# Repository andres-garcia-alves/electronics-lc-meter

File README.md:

# LC Meter v2.0

A Capacimeter + Inductometer based on Arduino Nano.  
Capacitor measurement with 3 working modes: accuracy (slow), balanced and speed.  

Case 3D model included ;-)

This proyect was inspired on video [Medidor de Bobinas/Inductores y Capacitores con Arduino y Display LCD](https://www.youtube.com/watch?v=hMa-AWyuxaA) (spanish) from [Electgpl](https://www.youtube.com/@electgpl) YouTube channel.

&nbsp;

This project use the following electronic components:
- 1 x Arduino Nano v3.0
- 1 x LCD Display 16x2
- 1 x LCD Display I2C Module
- 1 x LM358 Operational Amplifier
- 1 x Capacitor 1uF
- 1 x Switch Button (2 positions)
- 3 x Push Button
- 1 x 220 ohm resistor
- 1 x 470 ohm resistor
- 1 x 10K ohm resistor
- 1 x 100K ohm resistor
- 1 x 1M ohm resistor
- 14 x pin-header 90 degress
- 2 x Bornier x2 (optional)
- 1 x DC conector (optional power 5-12V)
- 2 x Alligator clip conector (optional external measurement)
- wires

&nbsp;

### Screenshots

| Diagram - Schematics                            | Diagram - PCB                                   |
|-------------------------------------------------|-------------------------------------------------|
|          |                |

| Diagram - PCB Render                            | Diagram - PCB Render                            |
|-------------------------------------------------|-------------------------------------------------|
|      |       |

| Prototype                                       | Prototype                                       |
|-------------------------------------------------|-------------------------------------------------|
|                  |                  |

| PCB Manufacturing                               | Project Assembly                                |
|-------------------------------------------------|-------------------------------------------------|
|          |               |

| PCB Assembly                                    | PCB Assembly                                    |
|-------------------------------------------------|-------------------------------------------------|
|               |               |

| Case 3D model                                   | Project Final                                   |
|-------------------------------------------------|-------------------------------------------------|
|              |              |

| Capacimeter (YouTube video)                     | Inductometer (YouTube video)                    |
|-------------------------------------------------|-------------------------------------------------|
|  |  |

See 'Rescources' sub-folder for more pictures & videos of the project.

&nbsp;

### Version History

v1.0 (2024.03.02) - Initial release.  
v1.1 (2024.03.03) - Adding case 3D model.  
v1.2 (2024.03.09) - Pin position & component annotations improvements.  
v1.3 (2025.12.20) - Update project structure.  
v1.4 (2025.12.26) - Adding 'Stickers' folder.  

&nbsp;

This source code is licensed under GPL v3.0  
Please send me your feedback about this project: andres.garcia.alves@gmail.com

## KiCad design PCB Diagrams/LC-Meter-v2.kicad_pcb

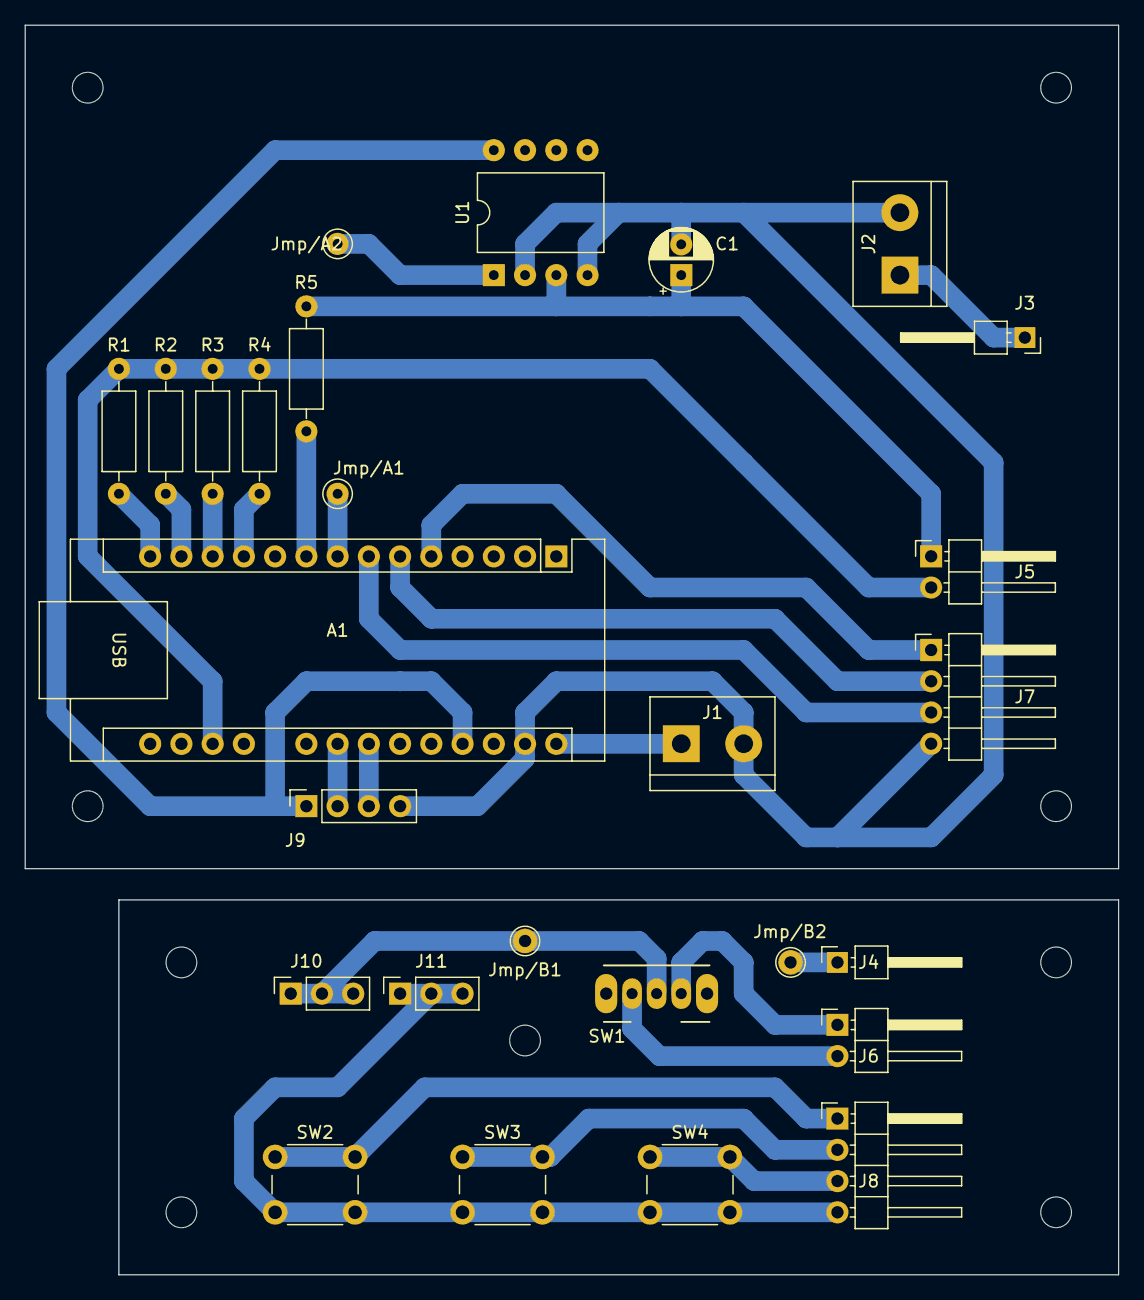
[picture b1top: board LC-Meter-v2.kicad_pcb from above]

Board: 2 copper layers, 88.9 x 101.6 mm, 36 parts (0 on the bottom side), 26 nets.

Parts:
A1: Arduino Nano v3; Arduino_Nano
C1: 1uF; CP_Radial_D5.0mm_P2.50mm
H1, H2, H3, H4: Base Hole; MountingHole_2.5mm
H5, H6, H7, H8, H9: Top Hole; MountingHole_2.5mm
J1: Power; TerminalBlock_bornier-2_P5.08mm
J2: External; TerminalBlock_bornier-2_P5.08mm
J3: Ext/A; PinHeader_1x01_P2.54mm_Horizontal
J4: Ext/B; PinHeader_1x01_P2.54mm_Horizontal
J5: Select/A; PinHeader_1x02_P2.54mm_Horizontal
J6: Select/B; PinHeader_1x02_P2.54mm_Horizontal
J7: CxMode/A; PinHeader_1x04_P2.54mm_Horizontal
J8: CxMode/B; PinHeader_1x04_P2.54mm_Horizontal
J9: Display I2C; PinSocket_1x04_P2.54mm_Vertical
J10: Cx/Lx; PinSocket_1x03_P2.54mm_Vertical
J11: GND; PinSocket_1x03_P2.54mm_Vertical
Jmp/A1, Jmp/A2: Bridge; TestPoint_THTPad_D2.0mm_Drill1.0mm
Jmp/B1, Jmp/B2: Bridge; TestPoint_THTPad_D2.0mm_Drill1.0mm
R1: 10k; R_Axial_DIN0207_L6.3mm_D2.5mm_P10.16mm_Horizontal
R2: 100k; R_Axial_DIN0207_L6.3mm_D2.5mm_P10.16mm_Horizontal
R3: 1M; R_Axial_DIN0207_L6.3mm_D2.5mm_P10.16mm_Horizontal
R4: 470; R_Axial_DIN0207_L6.3mm_D2.5mm_P10.16mm_Horizontal
R5: 220; R_Axial_DIN0207_L6.3mm_D2.5mm_P10.16mm_Horizontal
SW1: Select; SW_CuK_OS102011MA1QN1_SPDT_Angled
SW2: High; SW_PUSH_6mm_H7.3mm
SW3: Med; SW_PUSH_6mm_H7.3mm
SW4: Low; SW_PUSH_6mm_H7.3mm
U1: LM358; DIP-8_W10.16mm

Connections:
+5V: A1.27 (+5V), J9.1, U1.8 (V+)
+VDC: A1.30 (VIN), J1.1
GND: A1.29 (GND), C1.2, J1.2, J2.2, J7.4, J9.4, U1.2 (-), U1.4 (V-)
unnamed: A1.19 (A0), J5.2, R1.1, R2.1, R3.1, R4.1
unnamed: A1.23 (A4), J9.2
unnamed: A1.24 (A5), J9.3
unnamed: A1.5 (D2), J7.1
unnamed: A1.6 (D3), J7.2
unnamed: A1.7 (D4), J7.3
unnamed: A1.8 (D5), Jmp/A1.1
unnamed: A1.9 (D6), R5.2
unnamed: A1.11 (D8), R4.2
unnamed: A1.12 (D9), R3.2
unnamed: A1.13 (D10), R2.2
unnamed: A1.14 (D11), R1.2
unnamed: J2.1, J3.1
unnamed: J4.1, Jmp/B2.1
unnamed: C1.1, J5.1, R5.1, U1.3 (+)
unnamed: J6.1, SW1.3 (A)
unnamed: J6.2, SW1.1 (C)
unnamed: J8.1, SW2.1
unnamed: J8.2, SW3.1
unnamed: J8.3, SW4.1
unnamed: J10.1, J10.2, J10.3, Jmp/B1.1, SW1.2 (B)
unnamed: J8.4, J11.1, J11.2, J11.3, SW2.2, SW3.2, SW4.2
unnamed: Jmp/A2.1, U1.1

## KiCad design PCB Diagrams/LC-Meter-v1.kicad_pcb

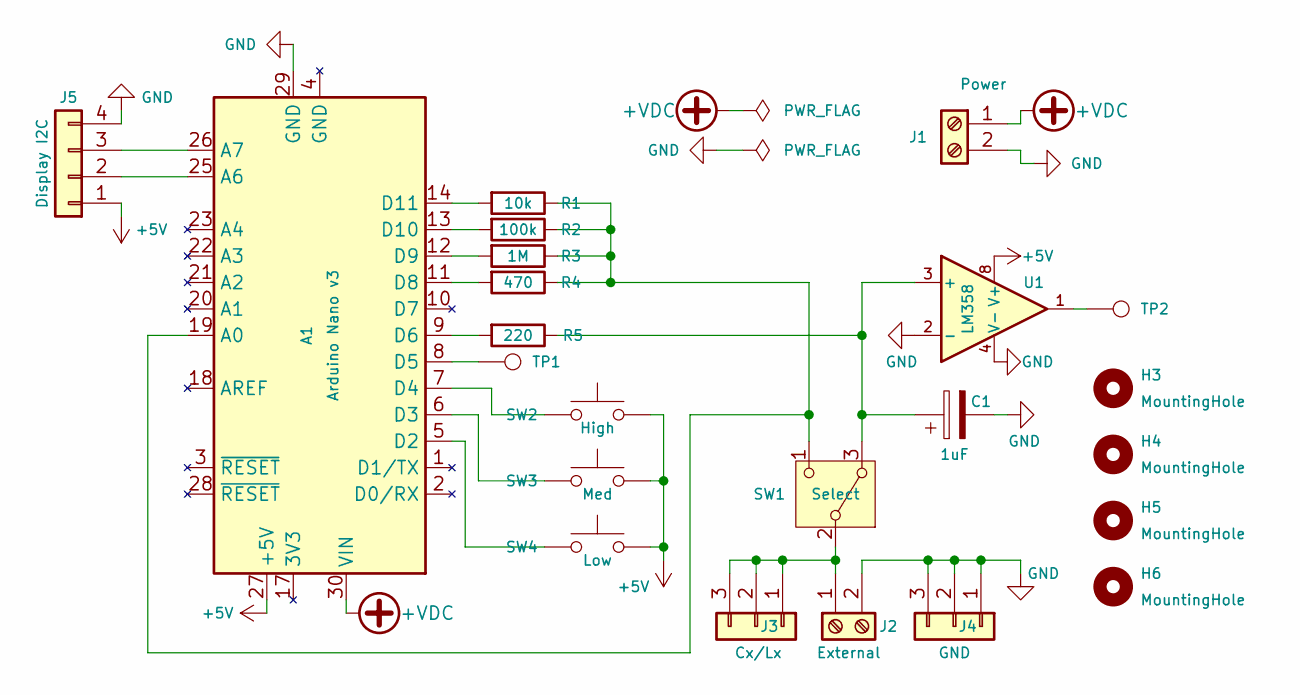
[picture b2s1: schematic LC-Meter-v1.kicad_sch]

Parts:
A1: Arduino Nano v3; Arduino_Nano
C1: 1uF; CP_Radial_D5.0mm_P2.50mm
H3, H4, H5, H6: MountingHole; MountingHole_2.5mm
J1: Power; TerminalBlock_bornier-2_P5.08mm
J2: External; TerminalBlock_bornier-2_P5.08mm
J3: Cx/Lx; PinSocket_1x03_P2.54mm_Vertical
J4: GND; PinSocket_1x03_P2.54mm_Vertical
J5: Display I2C; PinSocket_1x04_P2.54mm_Vertical
R1: 10k; R_Axial_DIN0207_L6.3mm_D2.5mm_P10.16mm_Horizontal
R2: 100k; R_Axial_DIN0207_L6.3mm_D2.5mm_P10.16mm_Horizontal
R3: 1M; R_Axial_DIN0207_L6.3mm_D2.5mm_P10.16mm_Horizontal
R4: 470; R_Axial_DIN0207_L6.3mm_D2.5mm_P10.16mm_Horizontal
R5: 220; R_Axial_DIN0207_L6.3mm_D2.5mm_P10.16mm_Horizontal
SW1: Select; SW_CuK_OS102011MA1QN1_SPDT_Angled
SW2: High; SW_PUSH_6mm_H7.3mm
SW3: Med; SW_PUSH_6mm_H7.3mm
SW4: Low; SW_PUSH_6mm_H7.3mm
TP1, TP2: Bridge; TestPoint_THTPad_D2.0mm_Drill1.0mm
U1: LM358; DIP-8_W10.16mm

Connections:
+5V: A1.27 (+5V), J5.1, SW2.2, SW3.2, SW4.2, U1.8 (V+)
+VDC: A1.30 (VIN), J1.1
GND: A1.29 (GND), C1.2, J1.2, J2.2, J4.1, J4.2, J4.3, J5.4, U1.2 (-), U1.4 (V-)
unnamed: A1.19 (A0), R1.1, R2.1, R3.1, R4.1, SW1.1 (C)
unnamed: A1.25 (A6), J5.2
unnamed: A1.26 (A7), J5.3
unnamed: A1.5 (D2), SW4.1
unnamed: A1.6 (D3), SW3.1
unnamed: A1.7 (D4), SW2.1
unnamed: A1.8 (D5), TP1.1
unnamed: A1.9 (D6), R5.2
unnamed: A1.11 (D8), R4.2
unnamed: A1.12 (D9), R3.2
unnamed: A1.13 (D10), R2.2
unnamed: A1.14 (D11), R1.2
unnamed: J2.1, J3.1, J3.2, J3.3, SW1.2 (B)
unnamed: C1.1, R5.1, SW1.3 (A), U1.3 (+)
unnamed: TP2.1, U1.1

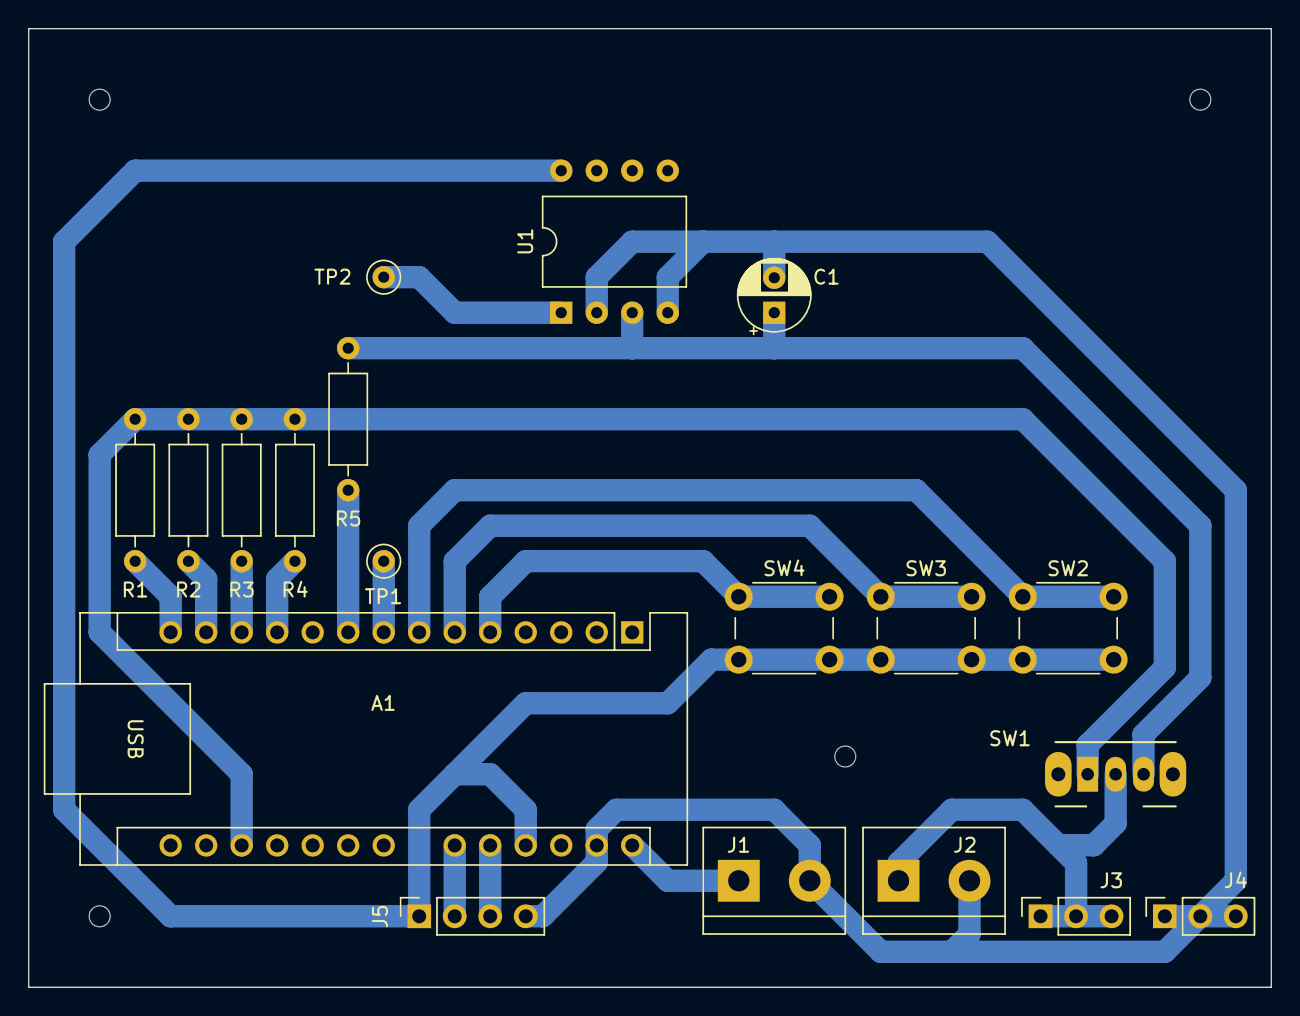
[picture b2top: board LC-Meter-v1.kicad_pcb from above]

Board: 2 copper layers, 88.9 x 68.6 mm, 23 parts (0 on the bottom side), 18 nets.

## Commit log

2024-02-19 first release
2024-03-04 adding case 3D model
2024-03-09 pin position & component annotations improvements
2025-12-20 update project structure
2025-12-26 Adding 'Stickers' folder
2026-02-02 Update Tracks
